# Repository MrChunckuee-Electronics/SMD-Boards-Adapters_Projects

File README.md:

# SMD_Adapters
Adaptadores SMD a Through-Hole.

***
Puedes seguirme en:
- [Blogspot](http://mrchunckuee.blogspot.com)
- [Instagram](https://www.instagram.com/mrchunckuee_electronics/)
- [Facebook](https://www.facebook.com/MrChunckueeElectronics)
- [Twitter](https://twitter.com/MrChunckuee)
- [YouTube](https://www.youtube.com/@MrChunckueeElectronics)

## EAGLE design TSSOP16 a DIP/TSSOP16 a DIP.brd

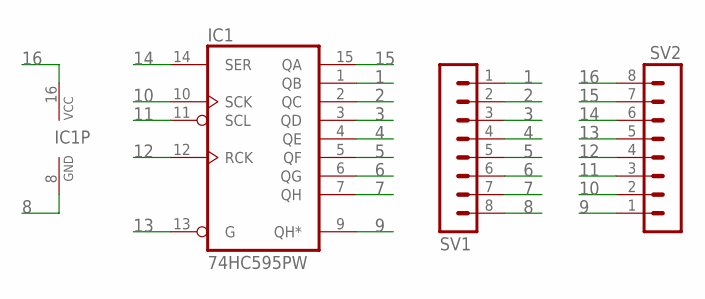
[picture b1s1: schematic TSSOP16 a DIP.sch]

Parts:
IC1: 74HC595PW; TSSOP16
SV1, SV2: MA08-1

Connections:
1: IC1.1 (QB), SV1.1
2: IC1.2 (QC), SV1.2
3: IC1.3 (QD), SV1.3
4: IC1.4 (QE), SV1.4
5: IC1.5 (QF), SV1.5
6: IC1.6 (QG), SV1.6
7: IC1.7 (QH), SV1.7
8: IC1.8 (GND), SV1.8
9: IC1.9 (QH*), SV2.1
10: IC1.10 (SCK), SV2.2
11: IC1.11 (SCL), SV2.3
12: IC1.12 (RCK), SV2.4
13: IC1.13 (G), SV2.5
14: IC1.14 (SER), SV2.6
15: IC1.15 (QA), SV2.7
16: IC1.16 (VCC), SV2.8

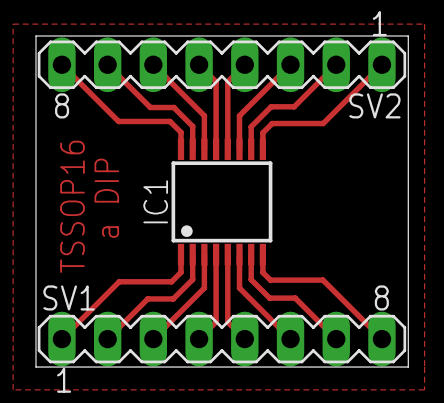
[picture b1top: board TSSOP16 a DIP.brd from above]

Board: 2 copper layers, 20.7 x 18.4 mm, 3 parts (0 on the bottom side), 16 nets.

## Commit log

2017-10-15 Adaptador TSSOP16 a DIP
